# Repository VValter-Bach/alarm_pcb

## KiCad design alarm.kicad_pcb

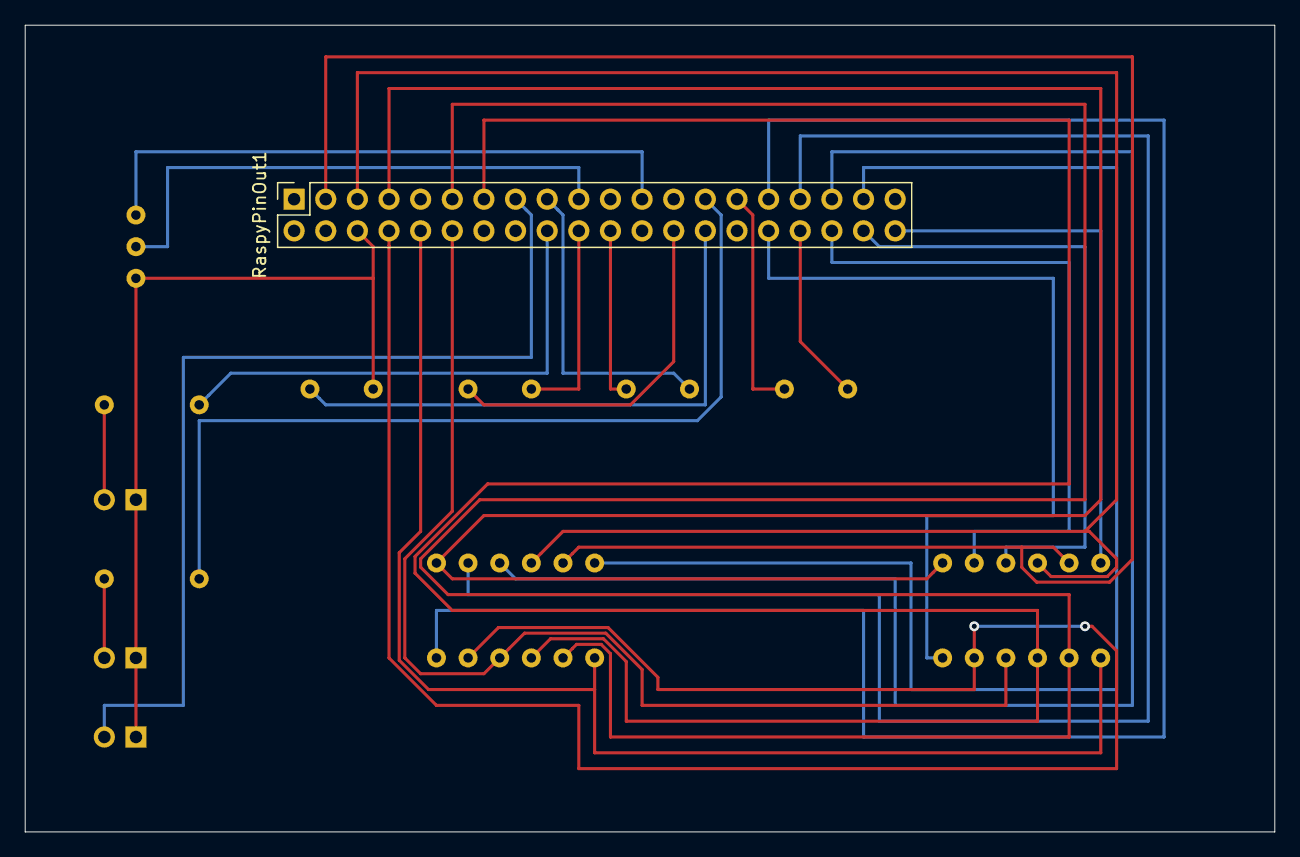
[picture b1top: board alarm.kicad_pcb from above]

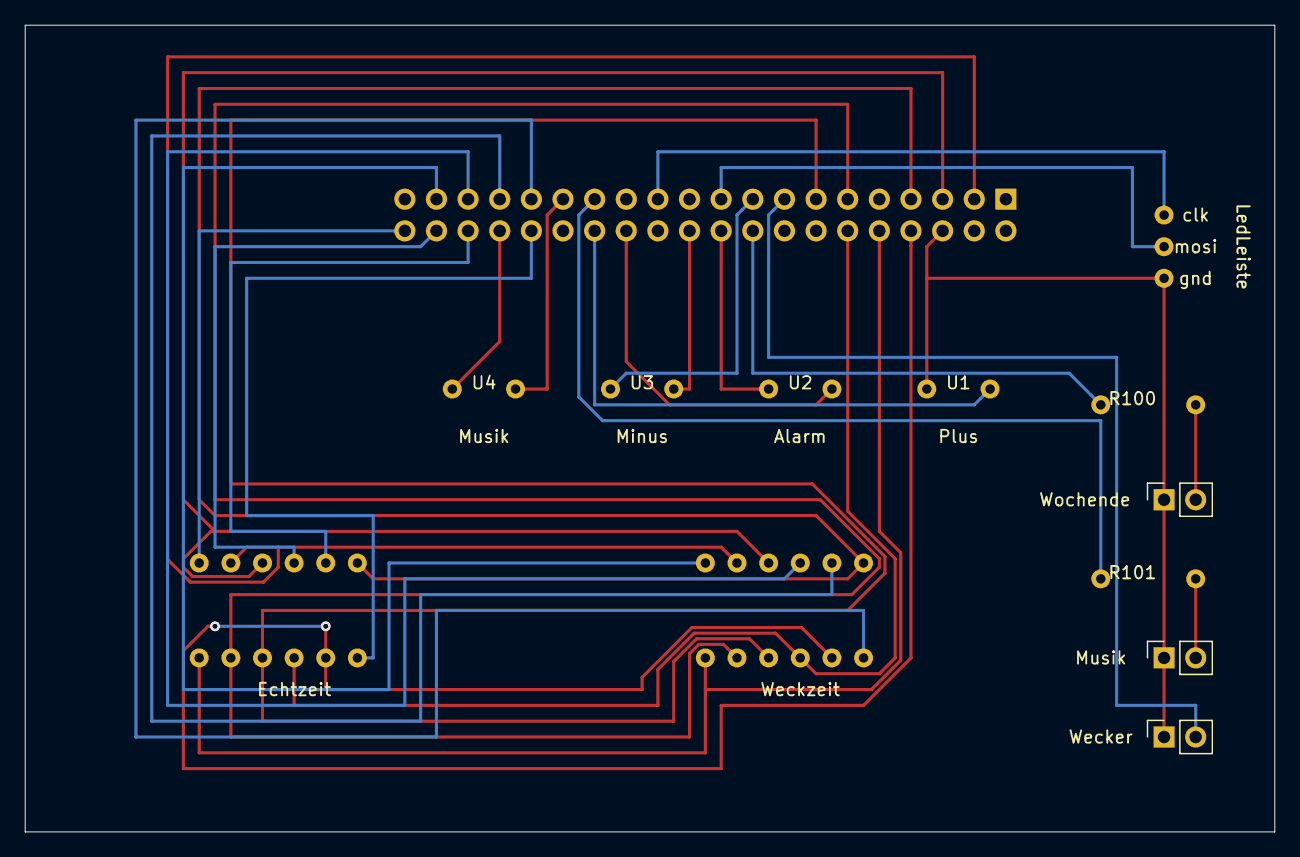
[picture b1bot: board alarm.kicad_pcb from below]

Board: 2 copper layers, 100.3 x 64.8 mm, 13 parts (12 on the bottom side), 29 nets.

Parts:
Echtzeit: 7Segment_2841; 7_Segment_2841A
LedLeiste: LedConnector; ledConnector
Musik: LED; PinSocket_1x02_P2.54mm_Vertical
R100, R101: Resitor; resistor
RaspyPinOut1: Raspberry_Pi_2_3; PinSocket_2x20_P2.54mm_Vertical
U1: add; button
U2: disable; button
U3: minus; button
U4: music; button
Wecker: LED; PinSocket_1x02_P2.54mm_Vertical
Weckzeit: 7Segment_2841; 7_Segment_2841A
Wochende: LED; PinSocket_1x02_P2.54mm_Vertical

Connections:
/clk: LedLeiste.3, RaspyPinOut1.23
/gnd: LedLeiste.1, Musik.1, RaspyPinOut1.6, RaspyPinOut1.9, RaspyPinOut1.14, RaspyPinOut1.20, RaspyPinOut1.25, RaspyPinOut1.30, RaspyPinOut1.34, RaspyPinOut1.39, U1.2, U2.2, U4.2, Wecker.1, Wochende.1
/mosi: LedLeiste.2, RaspyPinOut1.19
unnamed: Echtzeit.1, RaspyPinOut1.10, Weckzeit.1
unnamed: Echtzeit.2, RaspyPinOut1.11, Weckzeit.2
unnamed: Echtzeit.3, RaspyPinOut1.13, Weckzeit.3
unnamed: Echtzeit.4, RaspyPinOut1.12, Weckzeit.4
unnamed: Echtzeit.5, RaspyPinOut1.8, Weckzeit.5
unnamed: RaspyPinOut1.31, Weckzeit.6
unnamed: RaspyPinOut1.37, Weckzeit.7
unnamed: Echtzeit.8, RaspyPinOut1.3, Weckzeit.8
unnamed: Echtzeit.9, RaspyPinOut1.5, Weckzeit.9
unnamed: RaspyPinOut1.35, Weckzeit.10
unnamed: RaspyPinOut1.33, Weckzeit.11
unnamed: Echtzeit.12, RaspyPinOut1.7, Weckzeit.12
unnamed: R100.1, Wochende.2
unnamed: R100.2, RaspyPinOut1.18
unnamed: Musik.2, R101.1
unnamed: R101.2, RaspyPinOut1.27
unnamed: RaspyPinOut1.15, Wecker.2
unnamed: RaspyPinOut1.17, U3.2
unnamed: RaspyPinOut1.22, U3.1
unnamed: RaspyPinOut1.26, U2.1
unnamed: RaspyPinOut1.28, U1.1
unnamed: RaspyPinOut1.29, U4.1
unnamed: Echtzeit.6, RaspyPinOut1.32
unnamed: Echtzeit.11, RaspyPinOut1.36
unnamed: Echtzeit.10, RaspyPinOut1.38
unnamed: Echtzeit.7, RaspyPinOut1.40

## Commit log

2020-08-30 version 1 of alarm pcb, time will tell if it was correct
